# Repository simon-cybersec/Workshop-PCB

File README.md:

# Workshop-PCB

A nice little PCB for a soldering workshop I've done in the past. It has a mikrocontroller, a little OLED-display, a button, a LED and some SMD parts. \
When the button is pressed the display shows a text and the LED blinks, both for a time duration of ten minutes. The PCB is powered by a CR2032 coin cell battery.  

# The PCB design

The PCB is designed in order to be challenging but also to be fun to solder. Therefore the parts are surface mounted (SMD parts) with a size of 0805 which is kind of small, but not too small ;)  
 - The mikrocontroller is a [_STM32L062K8_](https://www.st.com/en/microcontrollers-microprocessors/stm32l062k8.html) from ST Microelectronics in a 32 pin LQFP package.

 - The OLED-display is bought from Amazon and is 1.3 inch in size. It communicates with the uC using the I2C protocol. The display is mounted on the main PCB with four screws.

 - For the processor clock an external crystal is used. It clocks with 8 MHz.  

 - Button debouncing is done in software in order to keep the PCB simple and because the workshop time was limited.  

# The parts

- Mikrocontroller \
[_STM32L062K8_](https://www.st.com/en/microcontrollers-microprocessors/stm32l062k8.html) (LQFP32 package)

- Button \
[_PTS636 SL43 SMTR LFS_](https://www.mouser.de/ProductDetail/CK/PTS636-SL43-SMTR-LFS?qs=vLWxofP3U2x0maTON%2FqK1g%3D%3D)

- Crystal \
[_ECS-80-18-4X-CKM_](https://www.mouser.de/ProductDetail/ECS/ECS-80-18-4X-CKM?qs=7MVldsJ5UazWVU6%2F43NmVA%3D%3D)

- 1.3 inch OLED display \
[_Link to Amazon_](https://www.amazon.de/AZDelivery-Display-Arduino-Raspberry-Gratis/dp/B078J78R45/ref=sr_1_2?__mk_de_DE=%C3%85M%C3%85%C5%BD%C3%95%C3%91&crid=2BH0U7SKDYO6I&keywords=oled%2B1.3&qid=1688516225&sprefix=oled%2B1.3%2Caps%2C98&sr=8-2&th=1)

- SMD LED \
[LG R971-KN-1](https://www.mouser.de/ProductDetail/ams-OSRAM/LG-R971-KN-1?qs=LsPilcdHE7EX1EB7GCLHxg%3D%3D) (size 0805)

- SMD capacitors and resistors (see down below)

- Pin header

- Coin battery _CR2032_

- SMD coin battery holder 

- screws and screw nuts (4x)
 
#### Capacitors (size 0805)
| Part | Value |
|------|-------|
| C1   | 10n   |
| C2   | 27p   |
| C3   | 27p   |
| C4   | 1u    |
| C5   | 100n  |
| C6   | 4.7u  |
| C7   | 100n  |
| C8   | 100n  |  

#### Resistors (size 0805)
| Part | Value |
|------|-------|
| R1   | 3k    |
| R2   | 2k    |
| R3   | 2k    |
| R4   | 200   |

# Eagle files
The files are located in the folder "_eagle-files_".  

# How to flash the uC
In order to flash the uC the _serial wire debug_ (SWD) protocol is used. The corresponding pins of the uC are layouted to the PCBs pinheader (have a look at the eagle files). I used a NUCLEO-development-board from ST, which is not only able to flash its own uC but also can flash external ones.  

# Note
Also have a look at my blog [simon-cybersec.github.io](https://simon-cybersec.github.io) which is all about embedded systems, cybersecurity and other crazy stuff ;)

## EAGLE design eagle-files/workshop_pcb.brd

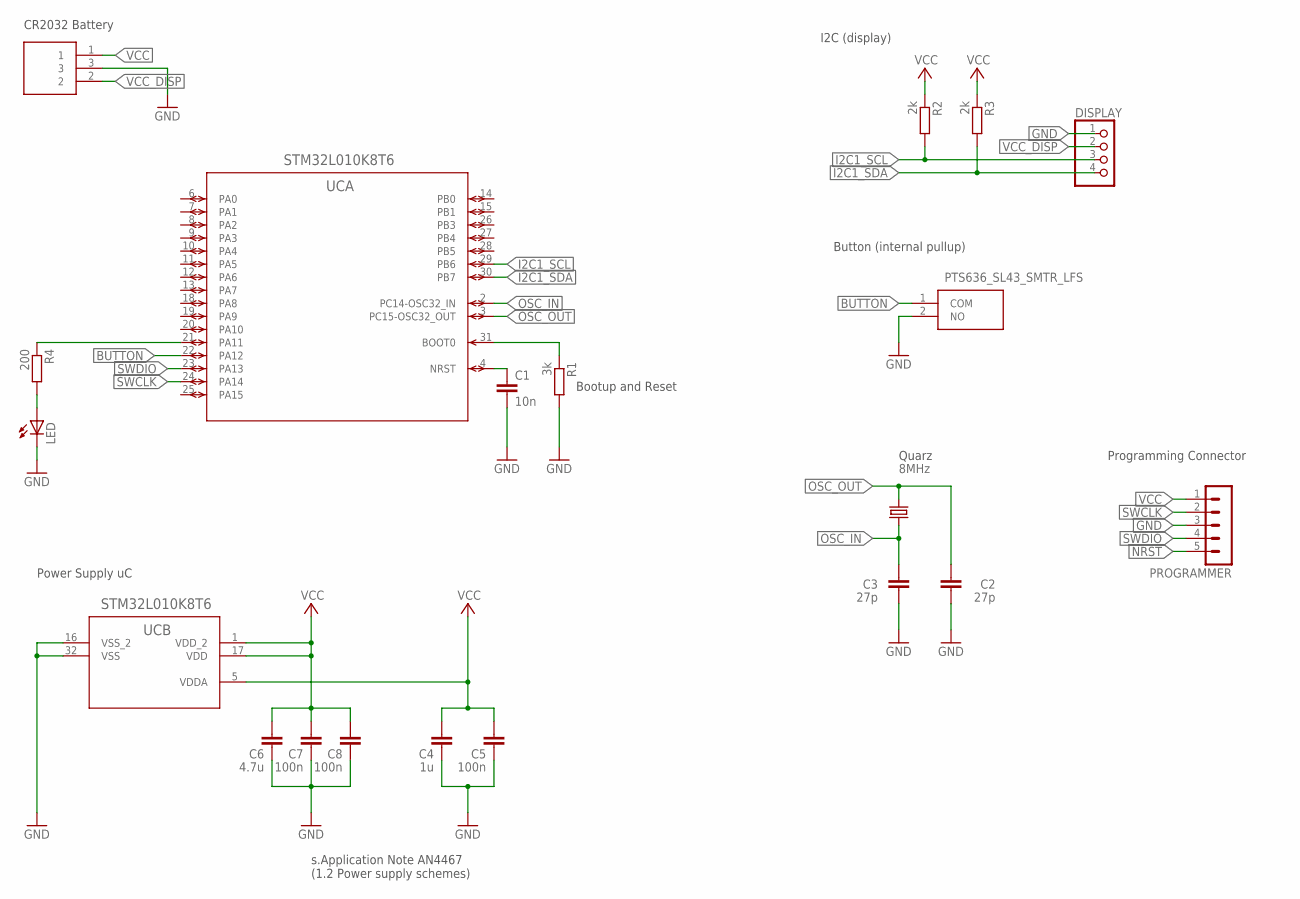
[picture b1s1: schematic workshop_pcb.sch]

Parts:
BUTTON: PTS636_SL43_SMTR_LFS; PTS636SL43SMTRLFS
C1: 10n; C0805
C2, C3: 27p; C0805
C4: 1u; C0805
C5, C7, C8: 100n; C0805
C6: 4.7u; C0805
CR2032: BAT-HLD-001; BATHLD001
DISPLAY: PINHD-1X4; 1X04
LED: LEDCHIPLED_0805; CHIPLED_0805
PROGRAMMER: MA05-1
QUARZ: 8MHz; HC49/S
R1: 3k; R0805
R2, R3: 2k; R0805
R4: 200; R0805
UC: STM32L010K8T6; LQFP32_7X7X1P4

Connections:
BOOT0: R1.1, UC.31 (BOOT0)
BUTTON: BUTTON.1 (COM), UC.22 (PA12)
GND: BUTTON.2 (NO), C1.2, C2.1, C3.1, C4.1, C5.1, C6.1, C7.1, C8.1, CR2032.3, DISPLAY.1, LED.C, PROGRAMMER.3, R1.2, UC.16 (VSS_2), UC.32 (VSS)
I2C1_SCL: DISPLAY.3, R2.2, UC.29 (PB6)
I2C1_SDA: DISPLAY.4, R3.2, UC.30 (PB7)
unnamed: LED.A, R4.2
unnamed: R4.1, UC.21 (PA11)
NRST: C1.1, PROGRAMMER.5, UC.4 (NRST)
OSC_IN: C3.2, QUARZ.2, UC.2 (PC14-OSC32_IN)
OSC_OUT: C2.2, QUARZ.1, UC.3 (PC15-OSC32_OUT)
SWCLK: PROGRAMMER.2, UC.24 (PA14)
SWDIO: PROGRAMMER.4, UC.23 (PA13)
VCC: C4.2, C5.2, C6.2, C7.2, C8.2, CR2032.1, PROGRAMMER.1, R2.1, R3.1, UC.1 (VDD_2), UC.5 (VDDA), UC.17 (VDD)
VCC_DISP: CR2032.2, DISPLAY.2

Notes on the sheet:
Bootup and Reset
Quarz
Power Supply uC
I2C (display)
Programming Connector
CR2032 Battery
s.Application Note AN4467 (1.2 Power supply schemes)
Button (internal pullup)

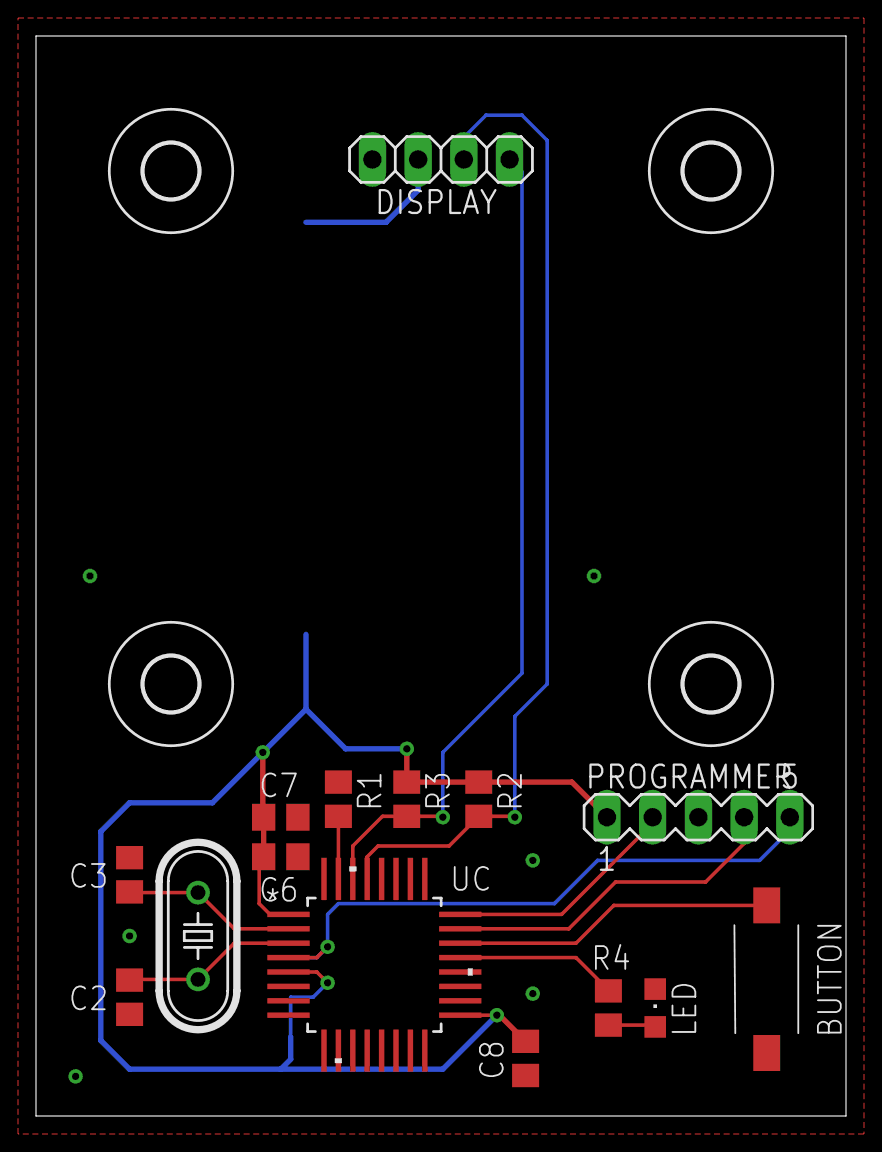
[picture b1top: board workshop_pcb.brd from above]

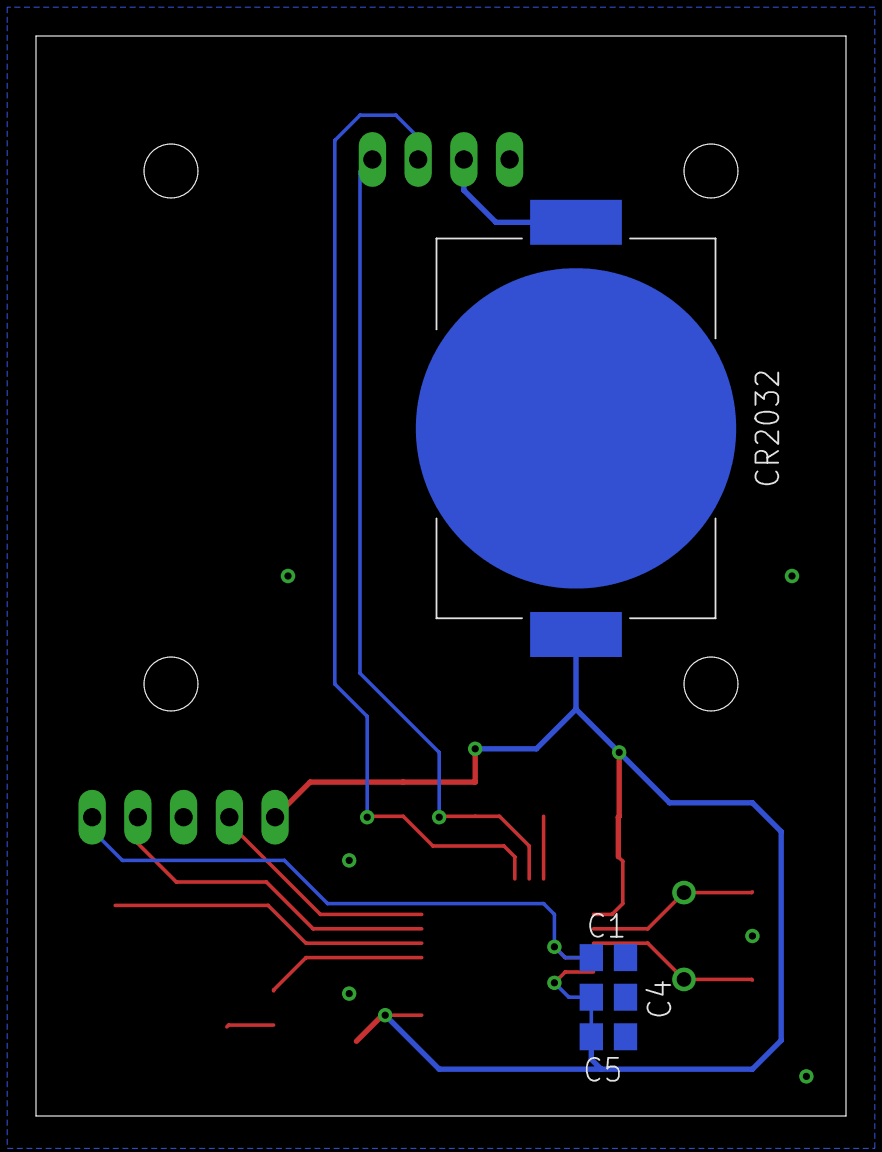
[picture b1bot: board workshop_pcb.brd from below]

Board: 2 copper layers, 45.0 x 60.0 mm, 23 parts (4 on the bottom side), 14 nets.

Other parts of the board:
U$1, U$2, U$3, U$4: 3,0

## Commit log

2023-07-05 Wrote documentation
2023-07-05 Updated blogpost
2023-07-05 Added section How to flash the uC
2023-07-05 Updated section How to flash the uC

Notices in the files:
parts and their libraries:
COPYRIGHT: Copyright (C) 2018 Accelerated Designs. All rights reserved
